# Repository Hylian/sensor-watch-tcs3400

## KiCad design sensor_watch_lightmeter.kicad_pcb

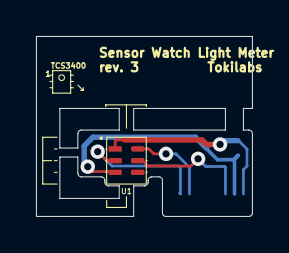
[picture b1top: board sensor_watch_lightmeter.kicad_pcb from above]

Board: 2 copper layers, 12.0 x 10.0 mm, 3 parts (1 on the bottom side), 5 nets.

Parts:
C1: 1uF; C_0201_0603Metric_Pad0.64x0.40mm_HandSolder
U1: TCS3400
U2: FH19C-9S-0.5SH_10-FFC; FH19C9S05SH10-FFC

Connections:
/A4_INT: U1.5 (INT), U2.3
/SCL: U1.2 (SCL), U2.8
/SDA: U1.6 (SDA), U2.7
GND: C1.2, U1.3 (GND), U2.2
VCC: C1.1, U1.1 (VDD), U2.1
